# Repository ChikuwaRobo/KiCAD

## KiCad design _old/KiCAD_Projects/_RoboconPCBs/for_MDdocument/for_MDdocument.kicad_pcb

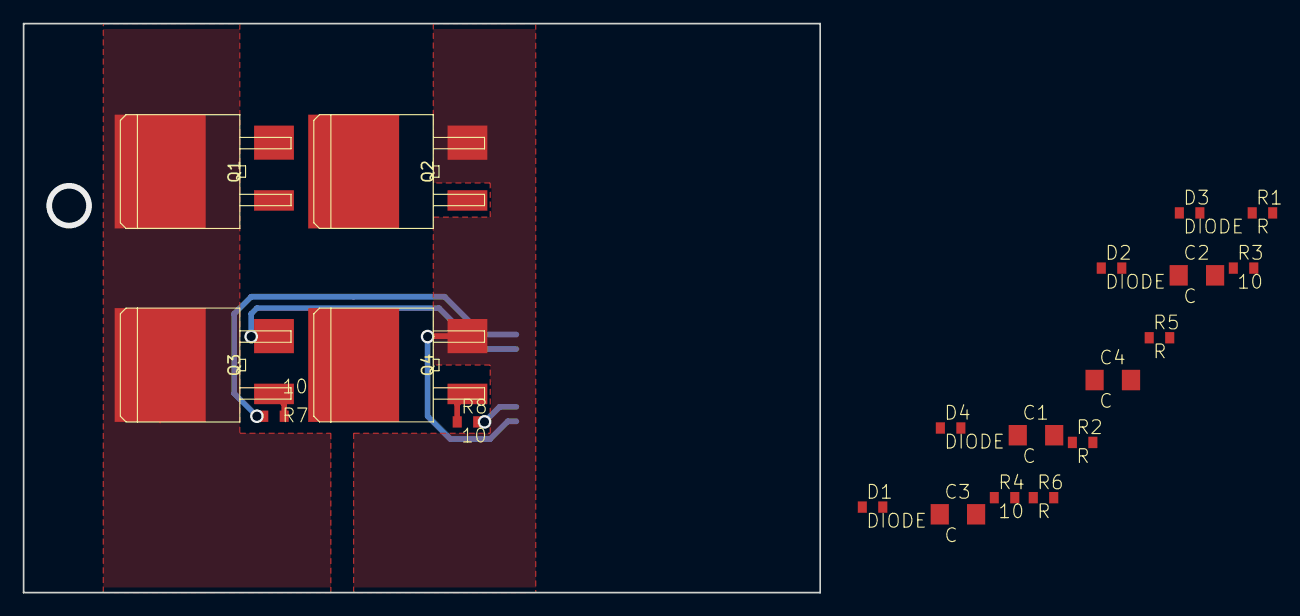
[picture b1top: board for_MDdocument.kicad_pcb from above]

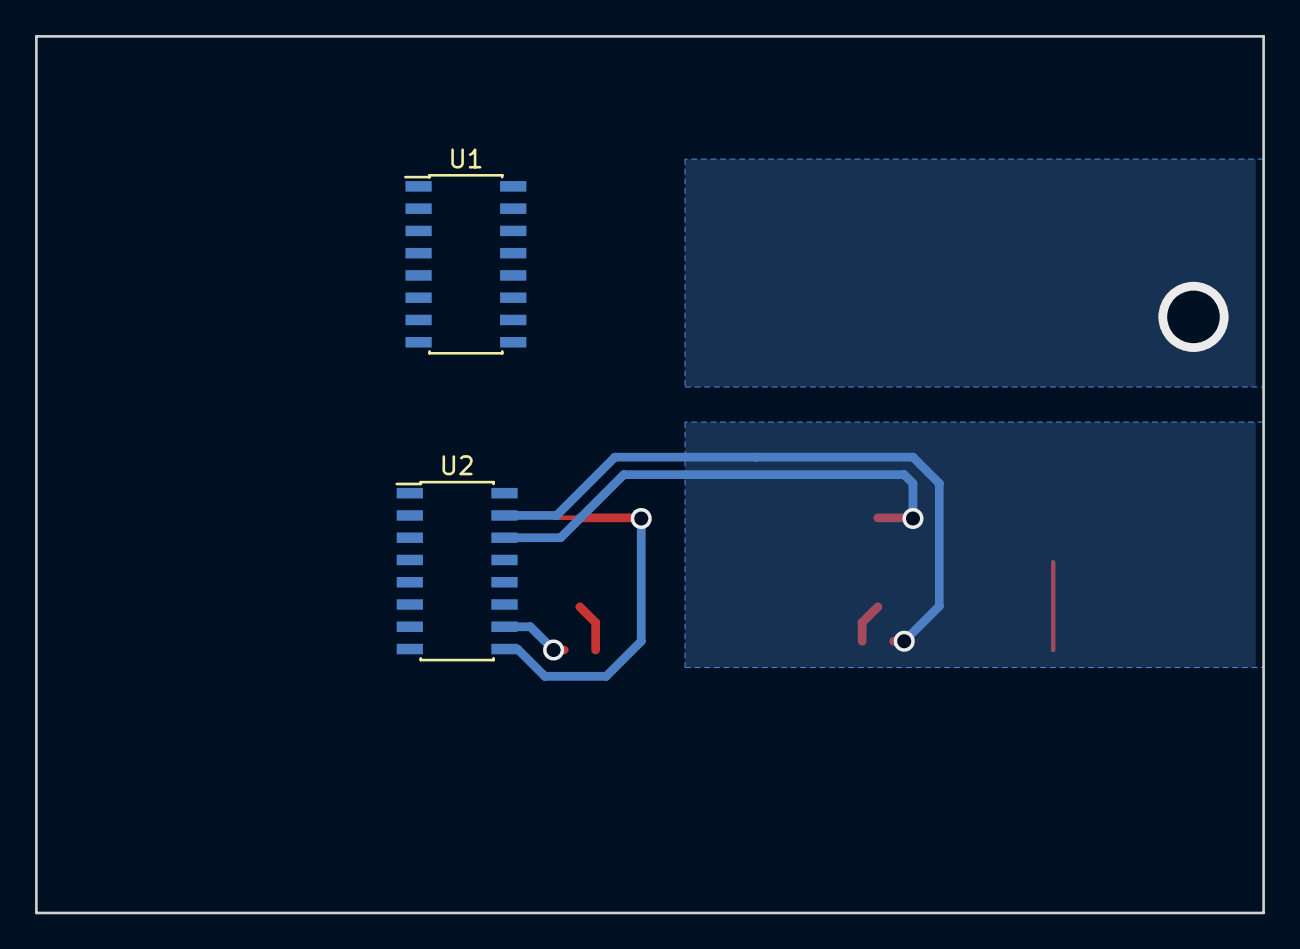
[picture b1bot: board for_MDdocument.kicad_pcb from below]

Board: 2 copper layers, 70.0 x 50.0 mm, 22 parts (2 on the bottom side), 21 nets.

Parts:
C1, C2, C3, C4: C; C3216
D1, D2, D3, D4: DIODE; C1608_WP
Q1, Q2, Q3, Q4: MOSFET_N; D2-PAK_compact
R1, R2, R5, R6: R; C1608_WP
R3, R4, R7, R8: 10; C1608_WP
U1, U2: SI8234; SOIC-16_3.9x9.9mm_Pitch1.27mm

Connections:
+BATT: Q1.D, Q3.D
/GD_12V: R1.1, R2.1, R5.1, R6.1
/OUT_A: C1.2, Q1.S, Q2.D, U1.14
/OUT_B: C3.2, Q3.S, Q4.D, U2.14
GNDPWR: C2.2, C4.2, Q2.S, Q4.S, U1.9, U2.9
unnamed: C1.1, D1.1, U1.16
unnamed: C2.1, D2.1, U1.11
unnamed: C3.1, D3.1, U2.16
unnamed: C4.1, D4.1, U2.11
unnamed: D1.2, R1.2
unnamed: D2.2, R2.2
unnamed: D3.2, R5.2
unnamed: D4.2, R6.2
unnamed: Q1.G, R3.1
unnamed: Q2.G, R4.1
unnamed: Q3.G, R7.1
unnamed: Q4.G, R8.1
unnamed: R3.2, U1.15
unnamed: R4.2, U1.10
unnamed: R7.2, U2.15
unnamed: R8.2, U2.10

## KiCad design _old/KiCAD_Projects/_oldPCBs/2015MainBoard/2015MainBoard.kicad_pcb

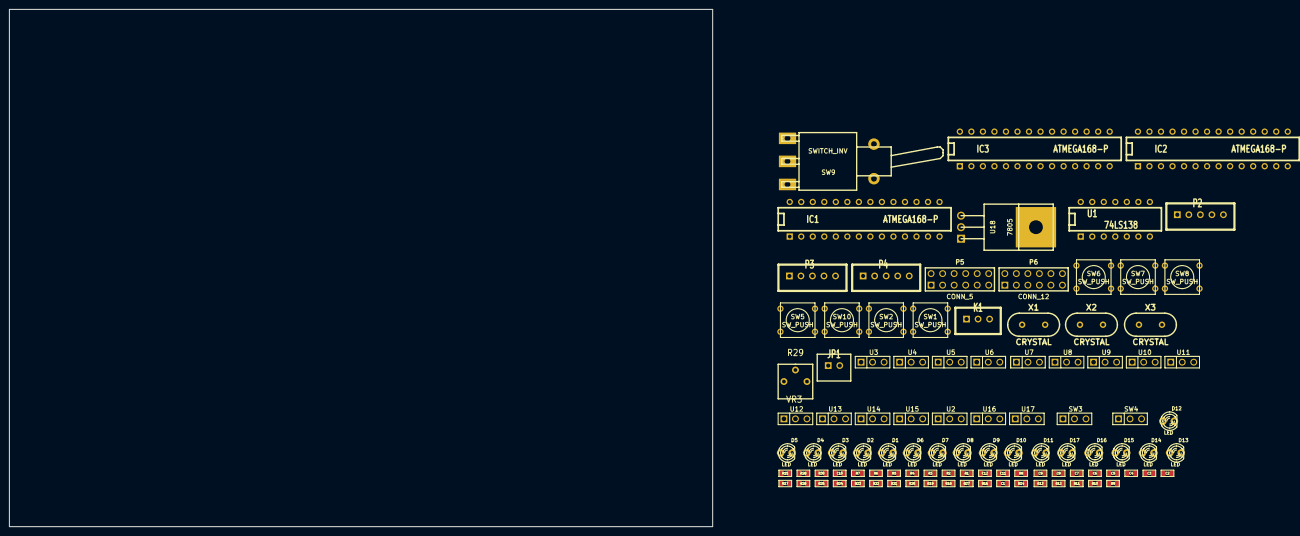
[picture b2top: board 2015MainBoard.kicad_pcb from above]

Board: 2 copper layers, 155.0 x 114.0 mm, 100 parts (0 on the bottom side), 73 nets, no tracks yet.

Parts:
C1, C2, C3, C4, C5, C6, C7, C8, C9, C10, C11, C12: C; SM0603
D1, D2, D3, D4, D5, D6, D7, D8, D9, D10, D11, D12, D13, D14, D15, D16, D17: LED; LED-3MM
IC1, IC2, IC3: ATMEGA168-P; DIP-28__300
JP1: JUMPER; XH2
K1: CONN_3; XH3
P2: DIL14; XH5
P3, P4: CONN_5; XH5
P5: CONN_5; pin_array_6x2
P6: CONN_12; pin_array_6x2
R1, R2, R3, R4, R5, R6, R7, R8, R9, R10, R11, R12, R13, R14, R15, R16, R17, R18, R19, R20, R21, R22, R23, R24, R25, R26, R27, R28, R30: R; SM0603
R29: VR3; RV2sq
SW1, SW2, SW5, SW6, SW7, SW8, SW10: SW_PUSH; SW_PUSH_SMALL
SW3, SW4: SWITCH_INV; PIN_ARRAY_3X1
SW9: SWITCH_INV; SW_SPDT
U1: 74LS138; DIP-14__300
U2, U3, U4, U5, U6, U7, U8, U9, U10, U11, U12, U13, U14, U15, U16, U17: IR; PIN_ARRAY_3X1
U18: 7805; TO220
X1, X2, X3: CRYSTAL; HC-49V

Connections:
+5V: C5.1, D2.1, D3.1, D4.1, D5.1, D6.1, D7.1, D8.1, D9.1, D10.1, D11.1, D12.1, D13.1, D14.1, D15.1, D16.1, D17.1, IC1.7, IC1.20, IC1.21, IC2.21, IC3.21, JP1.1, P3.1, P4.1, P5.1, P6.1, R2.1, R4.1, R15.1, R16.1, R17.2, R18.2, R28.1, R30.2, SW9.1, U2.3, U3.3, U4.3, U5.3, U6.3, U7.3, U8.3, U9.3, U10.3, U11.3, U12.3, U13.3, U14.3, U15.3, U16.3, U17.3
BallRST: IC2.1, P5.3, R1.2
BallRXD: IC2.2, P5.4, SW4.3
BallTXD: IC2.3, P5.5
DIS: D1.1, IC2.28
GND: C1.1, C2.1, C3.1, C4.1, C5.2, C6.2, C7.2, C8.1, C9.1, C10.2, C11.1, C12.1, IC1.8, IC1.22, IC2.22, IC3.22, K1.3, P3.2, P4.2, P5.2, P6.2, P6.5, P6.11, R5.2, R6.2, SW1.2, SW2.2, SW5.1, SW6.1, SW7.1, SW8.1, SW9.3, SW10.2, U1.8, U2.1, U3.1, U4.1, U5.1, U6.1, U7.1, U8.1, U9.1, U10.1, U11.1, U12.1, U13.1, U14.1, U15.1, U16.1, U17.1
IR0: IC2.14, R7.2, U2.2
IR1: IC2.15, R8.2, U3.2
IR2: IC2.16, R9.2, U4.2
IR3: IC2.17, R10.2, U5.2
IR4: IC2.18, R11.2, U6.2
IR5: IC2.19, R12.2, U7.2
IR6: IC2.23, R13.2, U8.2
IR7: IC2.24, R14.2, U9.2
IR8: IC2.25, R19.2, U10.2
IR9: IC2.26, R20.2, U11.2
IR10: IC2.4, R21.2, U12.2
IR11: IC2.5, R22.2, U13.2
IR12: IC2.6, R23.2, U14.2
IR13: IC2.11, R24.2, U15.2
IR14: IC2.12, R25.2, U16.2
IR15: IC2.13, R26.2, U17.2
MISO: IC1.18, IC3.18, P2.2
MODE: IC2.27, JP1.2, R6.1
MOSI: IC1.17, IC3.17, P2.1
MainRST: P3.3, R3.2
MainRXD_out: P3.4, SW3.1
MainTXD: IC1.3, SW4.2
MainTXD_out: P3.5, SW4.1
unnamed: C3.2, C4.2, IC2.10, X2.2
unnamed: IC3.4, P6.4
unnamed: IC3.5, P6.6
unnamed: IC3.11, P6.8
unnamed: IC3.13, P6.10
unnamed: P6.12, R30.1
unnamed: IC3.9, X3.1
unnamed: IC1.9, X1.1
unnamed: R1.1, R2.2, SW1.1
unnamed: R27.1, R28.2, SW10.1
unnamed: R3.1, R4.2, SW2.1
unnamed: IC3.12, P6.9
unnamed: IC3.6, P6.7
unnamed: U1.4, U1.5
unnamed: C1.2, C2.2, IC1.10, X1.2
unnamed: C11.2, C12.2, IC3.10, X3.2
unnamed: IC2.9, X2.1
unnamed: D2.2, R7.1
unnamed: D3.2, R8.1
unnamed: D4.2, R9.1
unnamed: D15.2, R24.1
unnamed: D16.2, R25.1
unnamed: D13.2, R22.1
unnamed: D14.2, R23.1
unnamed: D1.2, R5.1
unnamed: D17.2, R26.1
unnamed: D7.2, R12.1
unnamed: D6.2, R11.1
unnamed: D8.2, R13.1
unnamed: D5.2, R10.1
unnamed: D11.2, R20.1
unnamed: D12.2, R21.1
unnamed: D9.2, R14.1
unnamed: D10.2, R19.1
SCK: IC1.19, IC3.19, P2.3
SS1: P2.5, U1.14
SS3: IC3.16, U1.12
SW0: C6.1, IC1.4, R15.2, SW5.2
SW1: C7.1, IC1.6, R16.2, SW6.2
SW2: C8.2, IC1.25, R17.1, SW7.2
SW3: C9.2, IC1.26, R18.1, SW8.2
lcdRST: IC3.1, P4.3, R27.2
lcdRXD: IC3.2, P4.4
lcdTXD: IC3.3, P4.5

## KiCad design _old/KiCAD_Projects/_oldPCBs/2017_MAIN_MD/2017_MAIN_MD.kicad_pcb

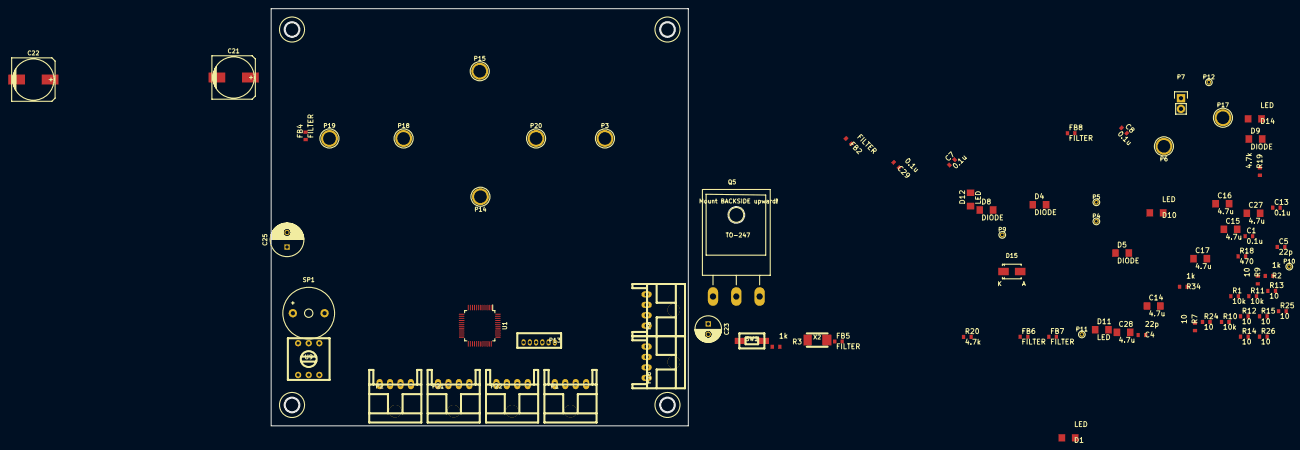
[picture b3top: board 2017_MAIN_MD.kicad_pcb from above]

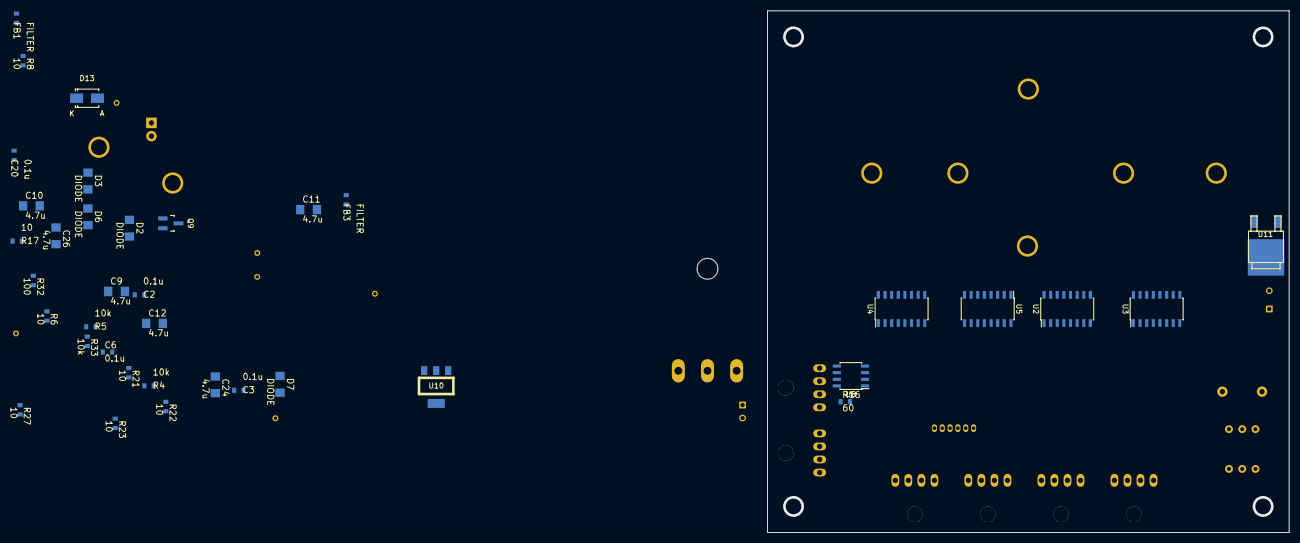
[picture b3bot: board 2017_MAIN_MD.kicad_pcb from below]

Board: 2 copper layers, 100.0 x 100.0 mm, 116 parts (37 on the bottom side), 87 nets, no tracks yet.

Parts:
C1, C2, C3, C6, C7, C8, C13, C20, C29: 0.1u; C1608_WP
C4, C5: 22p; C1608_WP
C9, C10, C11, C12, C14, C15, C16, C17, C24, C26, C27, C28: 4.7u; C3216
C21, C22: 470u; c_elec_10x10.5
C23: 100u; C_Radial_D6.3_L11.2_P2.5
C25: 100u; C_Radial_D8_L11.5_P3.5
D1, D10, D11, D12, D14: LED; C3216
D2, D3, D4, D5, D6, D7, D8, D9: DIODE; C3216
D13, D15: DIODE; SMA_Standard
FB1, FB2, FB3, FB4, FB5, FB6, FB7, FB8: FILTER; C1608_WP
P1, P2, P8, P16, P21, P22: CONN_01X04; XA_4LC
P3, P6, P14, P15, P17, P18, P19, P20: CONN_01X01; 1pin
P4, P5, P9, P10, P11, P12: TST; PINTST
P7: CONN_01X02; Pin_Header_Straight_1x02
P13: CONN_01X06; ZH_6T
Q5: MOSFET_N; TO-247_Horizontal_Neutral123_Reverse
Q9: MOSFET_N; SOT-23_Handsoldering
R1, R4, R5, R10, R11, R33: 10k; C1608_WP
R2, R3, R34: 1k; C1608_WP
R6, R7, R8, R9, R12, R13, R14, R15, R17, R21, R22, R23, R24, R25, R26, R27: 10; C1608_WP
R16: 60; C1608_WP
R18: 470; C1608_WP
R19, R20: 4.7k; C1608_WP
R32: 100; C1608_WP
SP1: SPEAKER; Buzzer_12x9.5RM7.6
SW1: SW_PUSH; RP_SMD_Button
U1: STM32F103_48; LQFP-48_7x7mm_Pitch0.5mm
U2, U3, U4, U5: SI8234; SOIC-16_3.9x9.9mm_Pitch1.27mm
U8: MAX3051; SOIC-8_3.9x4.9mm_Pitch1.27mm
U9: SW_ROTARY_16; rotary_0F
U10: NCP1117ST33T3G; TO-223
U11: NCP1117ST12T3G; SOT-428
X2: CRYSTAL; ABM3_2pads

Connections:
+3.3V: C2.2, C3.2, C6.2, C7.2, C8.2, C13.2, C20.2, C26.1, C29.2, D10.1, P1.2, P2.2, P5.1, P13.2, P21.2, P22.2, R1.1, U1.1, U1.9, U1.24, U1.36, U1.48, U2.3, U2.8, U3.3, U3.8, U4.3, U4.8, U5.3, U5.8, U8.3, U10.2
+12V: D11.1, D13.1, P8.2, P16.2, SP1.1
+BATT: C21.1, C22.1, D15.1, P14.1, P17.1, Q5.D
/BOOT0: R2.2, U1.44
/BUZZER: R32.2, U1.18
/CANH: P8.3, P16.3, R16.1, U8.7
/CANL: P7.1, P8.4, P16.4, U8.6
/CAN_RX: U1.32, U8.4
/CAN_TX: U1.33, U8.1
/ENC_Aa: P1.3, U1.10
/ENC_Ab: P1.4, U1.11
/ENC_Ba: P2.3, U1.16
/ENC_Bb: P2.4, U1.17
/GD_12V: C25.1, C28.1, D12.1, P12.1, R17.1, R21.1, R22.1, R23.1, R24.1, R25.1, R26.1, R27.1, U11.2
/LED_A: D14.1, U1.14
/LED_B: D1.1, U1.15
/LIMIT_A1: P21.3, U1.26
/LIMIT_A2: P21.4, U1.27
/LIMIT_B1: P22.3, U1.28
/LIMIT_B2: P22.4, U1.29
/MOTOR_EN: U1.25, U2.5, U3.5, U4.5, U5.5
/NRST: C1.2, R1.2, SW1.2, U1.7
/OSC_IN: C4.1, U1.5, X2.1
/OSC_OUT: C5.1, U1.6, X2.2
/OUT_A: C9.2, P18.1, U2.14
/OUT_AN: C11.2, P19.1, U3.14
/OUT_B: C14.2, P3.1, Q5.S, U4.14
/OUT_BN: C16.2, P20.1, U5.14
/PWM_A: U1.45, U2.1
/PWM_AN: U1.46, U3.1
/SEL_1: U1.19, U9.3
/SEL_2: U1.20, U9.1
/SEL_4: U1.21, U9.4
/SEL_8: U1.22, U9.6
/SWCLK: P13.3, U1.37
/SWDIO: P13.4, U1.34
/USART_RX: P13.6, U1.31
/USART_TX: P13.5, U1.30
GND: C1.1, C2.1, C3.1, C4.2, C5.2, C6.1, C7.1, C8.1, C13.1, C20.1, C23.2, C24.2, C26.2, C29.1, P1.1, P2.1, P8.1, P9.1, P13.1, P16.1, P21.1, P22.1, Q9.S, R2.1, R3.2, R4.2, R5.2, R10.2, R11.2, R18.2, R19.2, R33.2, R34.2, SW1.1, U1.8, U1.23, U1.35, U1.47, U2.4, U3.4, U4.4, U5.4, U8.2, U8.8, U9.2, U9.5, U10.1
GNDPWR: C10.2, C12.2, C15.2, C17.2, C21.2, C22.2, C25.2, C27.2, C28.2, P6.1, P11.1, P15.1, R20.2, U2.9, U3.9, U4.9, U5.9, U11.1
unnamed: C9.1, D2.2, U2.16
unnamed: C10.1, D6.2, U2.11
unnamed: C11.1, D3.2, U3.16
unnamed: C12.1, D7.2, U3.11
unnamed: C14.1, D4.2, U4.16
unnamed: C15.1, D8.2, U4.11
unnamed: C16.1, D5.2, U5.16
unnamed: C17.1, D9.2, U5.11
unnamed: C23.1, C24.1, D13.2, P4.1, U10.3
unnamed: C27.1, D15.2, P10.1, U11.3
unnamed: D1.2, R3.1
unnamed: D2.1, R21.2
unnamed: D3.1, R22.2
unnamed: D4.1, R17.2
unnamed: D5.1, R24.2
unnamed: D6.1, R23.2
unnamed: D7.1, R27.2
unnamed: D8.1, R25.2
unnamed: D9.1, R26.2
unnamed: D10.2, R18.1
unnamed: D11.2, R19.1
unnamed: D12.2, R20.1
unnamed: D14.2, R34.1
unnamed: FB1.1, R6.1
unnamed: FB2.1, R7.1
unnamed: FB3.1, R8.1
unnamed: FB4.1, R9.1
unnamed: FB5.1, R12.1
unnamed: FB5.2, Q5.G
unnamed: FB6.1, R13.1
unnamed: FB7.1, R14.1
unnamed: FB8.1, R15.1
unnamed: P7.2, R16.2
unnamed: Q9.D, SP1.2
unnamed: Q9.G, R32.1, R33.1
unnamed: R4.1, U2.6
unnamed: R5.1, U3.6
unnamed: R6.2, U2.15
unnamed: R7.2, U2.10
unnamed: R8.2, U3.15
unnamed: R9.2, U3.10
unnamed: R10.1, U4.6
unnamed: R11.1, U5.6
unnamed: R12.2, U4.15
unnamed: R13.2, U4.10
unnamed: R14.2, U5.15
unnamed: R15.2, U5.10

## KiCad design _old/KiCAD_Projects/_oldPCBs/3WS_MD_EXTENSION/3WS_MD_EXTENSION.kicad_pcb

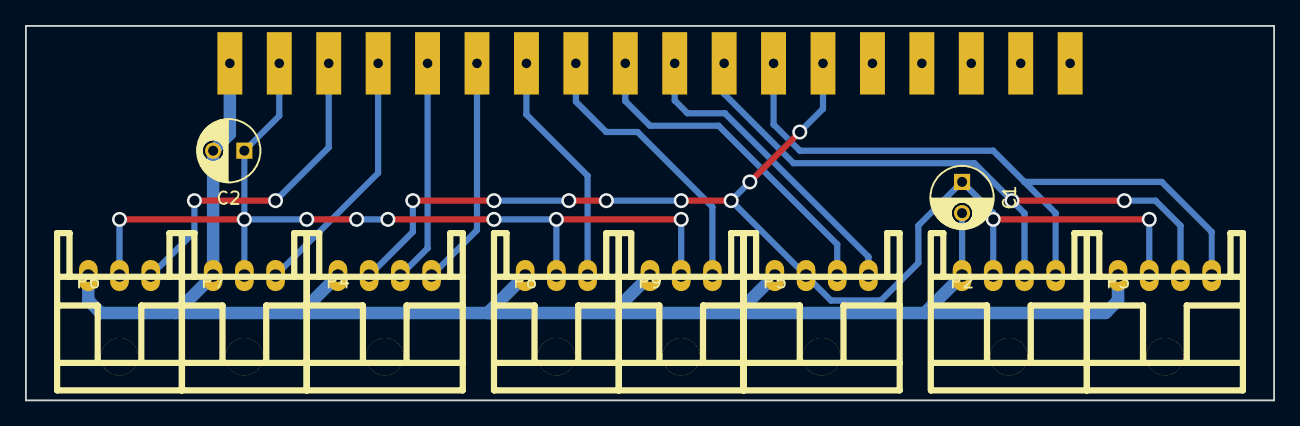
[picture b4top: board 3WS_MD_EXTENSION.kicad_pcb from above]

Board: 2 copper layers, 100.0 x 30.0 mm, 11 parts (1 on the bottom side), 13 nets.

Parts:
C1, C2: C; C_Radial_D5_L6_P2.5
P1: CONN_01X18; CardEdge_22(44type)_3.96mm_F
P2, P3, P4, P5: CONN_01X04; XA_4LC
P6, P7, P8, P9: CONN_01X03; XA_3LC

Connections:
+3.3V: C2.1, P1.2, P6.2, P7.2, P8.2, P9.2
+12V: C1.1, P1.13, P2.2, P3.2, P4.2, P5.2
/CAN_H: P1.11, P2.3, P3.3
/CAN_L: P1.12, P2.4, P3.4
/ENC_Aa: P1.5, P4.3
/ENC_Ab: P1.6, P4.4
/ENC_Ba: P1.9, P5.3
/ENC_Bb: P1.10, P5.4
/LIMIT_A1: P1.3, P6.3
/LIMIT_A2: P1.4, P7.3
/LIMIT_B1: P1.7, P8.3
/LIMIT_B2: P1.8, P9.3
GND: C1.2, C2.2, P1.1, P2.1, P3.1, P4.1, P5.1, P6.1, P7.1, P8.1, P9.1

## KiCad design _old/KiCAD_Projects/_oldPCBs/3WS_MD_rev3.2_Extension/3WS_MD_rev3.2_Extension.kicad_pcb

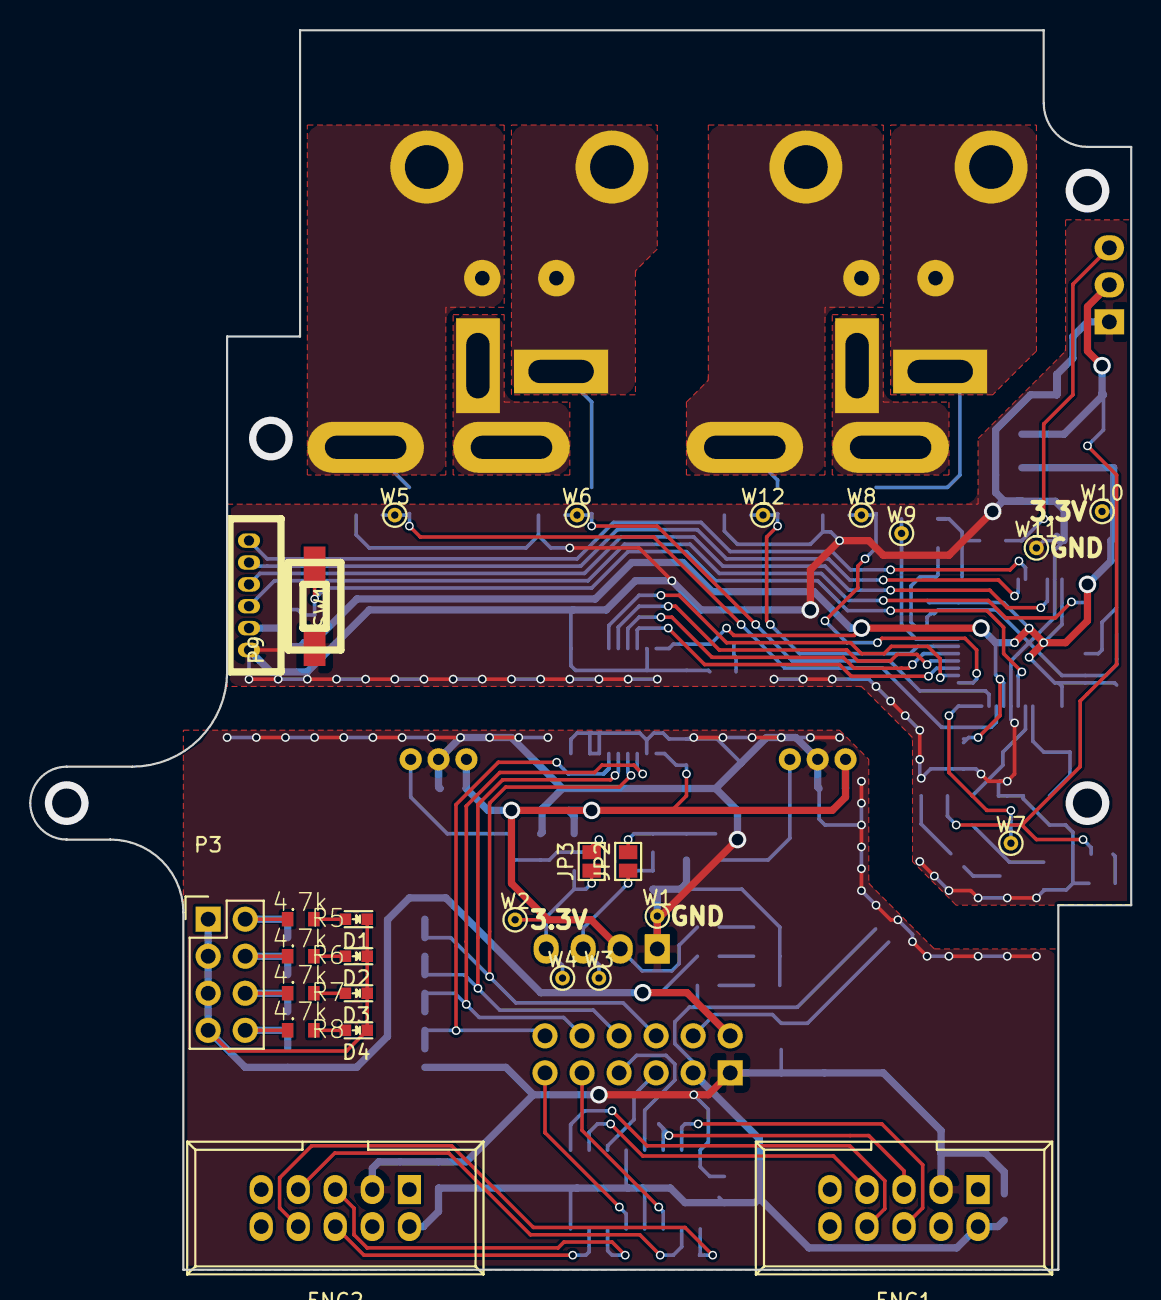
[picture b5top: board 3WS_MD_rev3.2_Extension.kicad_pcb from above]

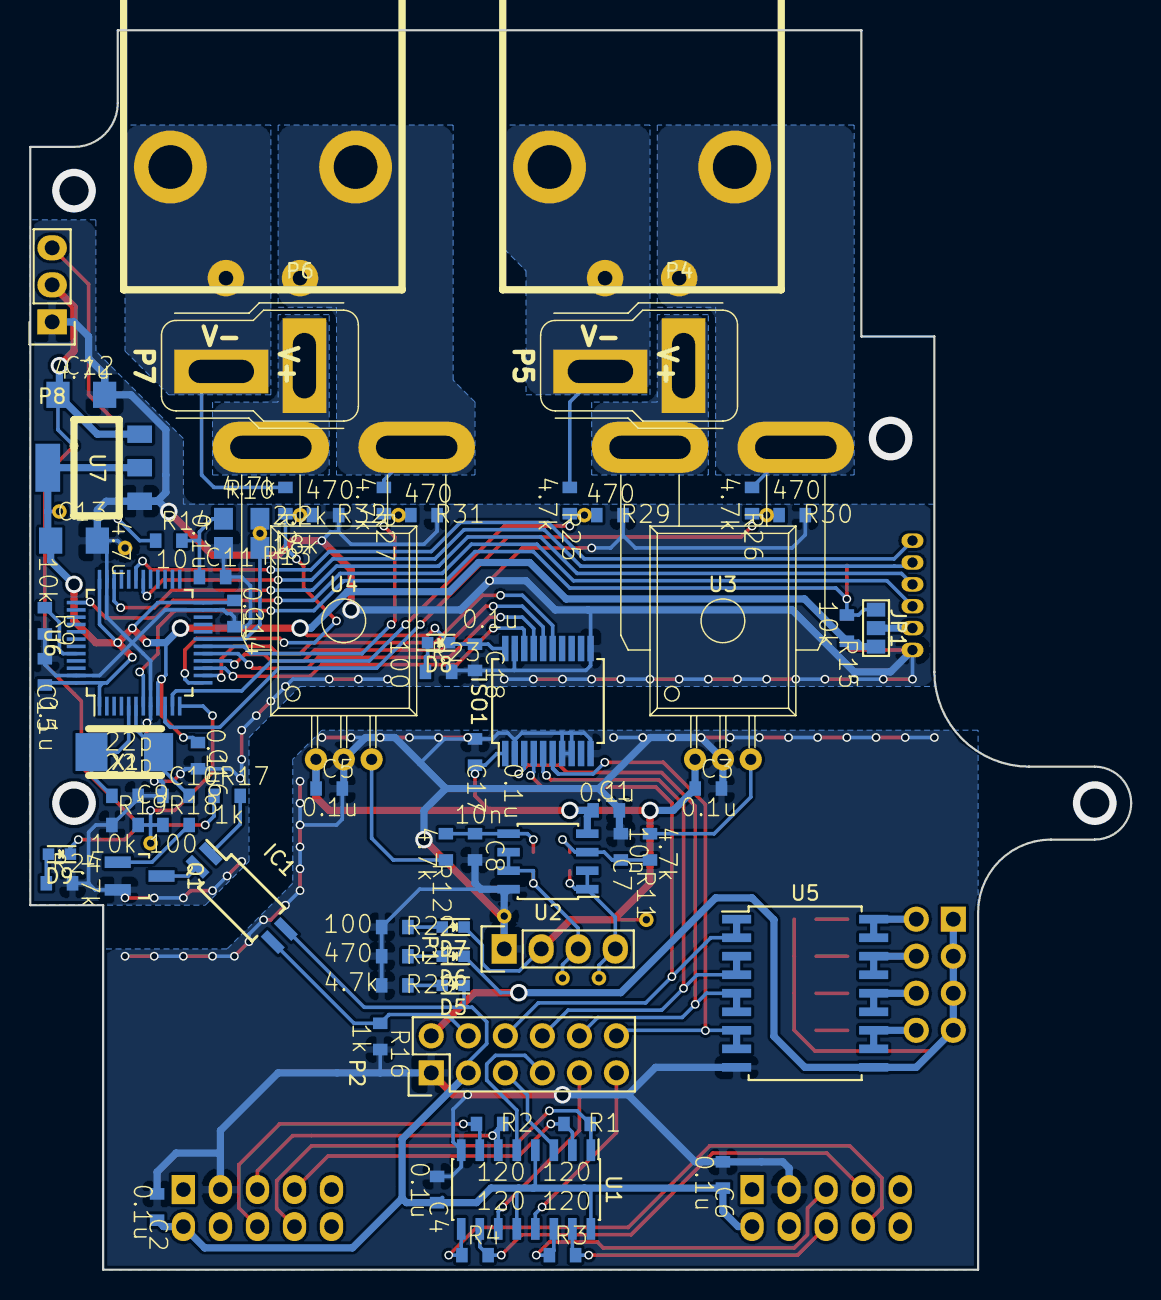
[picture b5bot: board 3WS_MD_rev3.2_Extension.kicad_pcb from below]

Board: 2 copper layers, 75.5 x 85.0 mm, 97 parts (70 on the bottom side), 73 nets.

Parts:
C1, C2, C3, C4, C5, C6, C11, C14, C15, C16, C17, C18: 0.1u; C1608_WP
C7, C8: 10n; C1608_WP
C9, C10: 22p; C1608_WP
C12, C13: 4.7u; C3216
D1, D2, D3, D4, D5, D6, D7, D8, D9: LED; LED_0603
ENC1, ENC2: RS422_ENCODER; DEF_ENCODER
IC1: TLP291; SOIJ-4_5.3x5.3mm_Pitch1.27mm
ISO1: ADuM3154; SSOP-20_5.3x7.2mm_Pitch0.65mm
JP1: JUMPER3; GS3
JP2, JP3: JUMPER; GS2
P1: CONN_01X04; Pin_Header_Straight_1x04
P2: CONN_02X06; Pin_Header_Straight_2x06
P3: CONN_02X04; Pin_Header_Straight_2x04
P4, P6: CONN_01X02; D-3200S_2L_PW
P5, P7: CONN_01X02; DEANS_T_M
P8: CONN_01X03; Pin_Header_Straight_1x03
P9: CONN_01X06; ZH_6T
Q1: MOSFET_N; SOT-23_Handsoldering
R1, R2, R3, R4: 120; C1608_WP
R5, R6, R7, R8, R11, R12, R20, R24, R25, R26, R27, R28: 4.7k; C1608_WP
R9, R15, R19: 10k; C1608_WP
R10: 18k; C2012
R13: 2.2k; C2012
R14: 10; C1608_WP
R16, R17: 1k; C1608_WP
R18, R22, R23: 100; C1608_WP
R21, R29, R30, R31, R32: 470; C1608_WP
SW1: SW_PUSH; RP_SMD_Button
U1: SN75175; SOIC-16_3.9x9.9mm_Pitch1.27mm
U2: LM358; SOIC-8_3.9x4.9mm_Pitch1.27mm
U3, U4: ACS758; ACS785xCB
U5: TBD62083A; SOIC-18_7.5x11.6mm_Pitch1.27mm
U6: STM32F103_48; LQFP-48_7x7mm_Pitch0.5mm
U7: NCP1117ST33T3G; SOT-223_reg
W1, W2, W3, W4, W5, W6, W7, W8, W9, W10, W11, W12: TEST_1P; PINTST
X1: CRYSTAL; ABM3_2pads

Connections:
+3.3V: C1.1, C3.1, C5.1, C17.1, D7.1, ISO1.1, P1.2, U2.4, U3.1, U4.1, W2.1
+5V: C2.1, C4.1, C6.1, D5.1, ENC1.2, ENC2.2, IC1.4, P2.3, U1.4, U1.12, U1.16
+12V: D1.1, D2.1, D3.1, D4.1, D6.1, P2.2, P3.1, P3.3, P3.5, P3.7, U5.10
+BATT: P8.3, R14.1
/BATT_IN: R10.2, R13.1, U6.19, W9.1
/ENC_Aa: P2.5, U1.3
/ENC_Aaa: ENC1.7, R1.2, U1.2
/ENC_Aab: ENC1.8, R1.1, U1.1
/ENC_Ab: P2.7, U1.5
/ENC_Aba: ENC1.5, R2.1, U1.6
/ENC_Abb: ENC1.6, R2.2, U1.7
/ENC_Ba: P2.9, U1.11
/ENC_Baa: ENC2.7, R4.2, U1.10
/ENC_Bab: ENC2.8, R4.1, U1.9
/ENC_Bb: P2.11, U1.13
/ENC_Bba: ENC2.5, R3.1, U1.14
/ENC_Bbb: ENC2.6, R3.2, U1.15
/EXIO_0: JP2.1, P1.3, U2.6, U2.7, W3.1
/EXIO_1: JP3.1, P1.4, U2.1, U2.2, W4.1
/GD_12V: C12.1, D9.1, P8.2, R17.1, U7.3
/NRST: JP1.1, R15.2, SW1.1, U6.7
/OUT_0: P3.2, R5.2, U5.17, U5.18
/OUT_1: P3.4, R6.2, U5.15, U5.16
/OUT_2: P3.6, R7.2, U5.13, U5.14
/OUT_3: P3.8, R8.2, U5.11, U5.12
/PW_3.3V: C13.1, C14.1, C15.1, C16.1, C18.1, D8.1, ISO1.20, JP1.3, R15.1, U6.1, U6.9, U6.24, U6.36, U6.48, U7.2, W10.1
/SPI_MISO: ISO1.16, U6.16
/SPI_MOSI: ISO1.17, U6.17
/SPI_NSS: ISO1.15, U6.14
/SPI_SCK: ISO1.18, U6.15
/SWDCK: P9.3, U6.37
/SWDIO: P9.4, U6.34
/USART_RX: P9.6, U6.31
/USART_TX: P9.5, U6.30
/V0A_IN: R27.1, R31.2, W12.1
/V0B_IN: R28.1, R32.2, U6.13, W8.1
/V1A_IN: R26.1, R30.2, U6.10, W5.1
/V1B_IN: R25.1, R29.2, U6.11, W6.1
/VALVE_0: ISO1.6, P2.12, U5.7, U5.8
/VALVE_1: ISO1.3, P2.10, U5.5, U5.6
/VALVE_2: ISO1.5, P2.8, U5.3, U5.4
/VALVE_3: ISO1.4, P2.6, U5.1, U5.2
/V_0A: P6.1, R27.2, U4.4
/V_0B: P6.2, P7.2, R28.2
/V_1A: P4.1, R26.2, U3.4
/V_1B: P4.2, P5.2, R25.2
/V_RX: IC1.3, P2.4, R16.1
/V_TX: R18.1, R19.2, U6.12, W7.1
GND: C1.2, C2.2, C3.2, C4.2, C5.2, C6.2, C7.2, C8.2, C17.2, ENC1.3, ENC2.3, ISO1.2, ISO1.7, ISO1.8, ISO1.10, P1.1, P2.1, R16.2, R20.2, R21.2, R22.2, U1.8, U2.8, U3.2, U4.2, U5.9, W1.1
GNDPWR: C9.1, C10.1, C11.2, C12.2, C13.2, C14.2, C15.2, C16.2, C18.2, ISO1.11, ISO1.19, P8.1, P9.1, Q1.S, R9.2, R13.2, R19.1, R23.2, R24.2, R29.1, R30.1, R31.1, R32.1, SW1.2, U6.8, U6.23, U6.35, U6.47, U7.1, W11.1
unnamed: C7.1, JP3.2, R11.2, U2.3
unnamed: C8.1, JP2.2, R12.2, U2.5
unnamed: C9.2, U6.5, X1.1
unnamed: C10.2, U6.6, X1.2
unnamed: C11.1, R10.1, R14.2
unnamed: D1.2, R5.1
unnamed: D2.2, R6.1
unnamed: D3.2, R7.1
unnamed: D4.2, R8.1
unnamed: D5.2, R20.1
unnamed: D6.2, R21.1
unnamed: D7.2, R22.1
unnamed: D8.2, R23.1
unnamed: D9.2, R24.1
unnamed: IC1.1, R17.2
unnamed: IC1.2, Q1.D
unnamed: JP1.2, P9.2
unnamed: P5.1, U3.5
unnamed: P7.1, U4.5
unnamed: Q1.G, R18.2
unnamed: R9.1, U6.44
unnamed: R11.1, U3.3
unnamed: R12.1, U4.3

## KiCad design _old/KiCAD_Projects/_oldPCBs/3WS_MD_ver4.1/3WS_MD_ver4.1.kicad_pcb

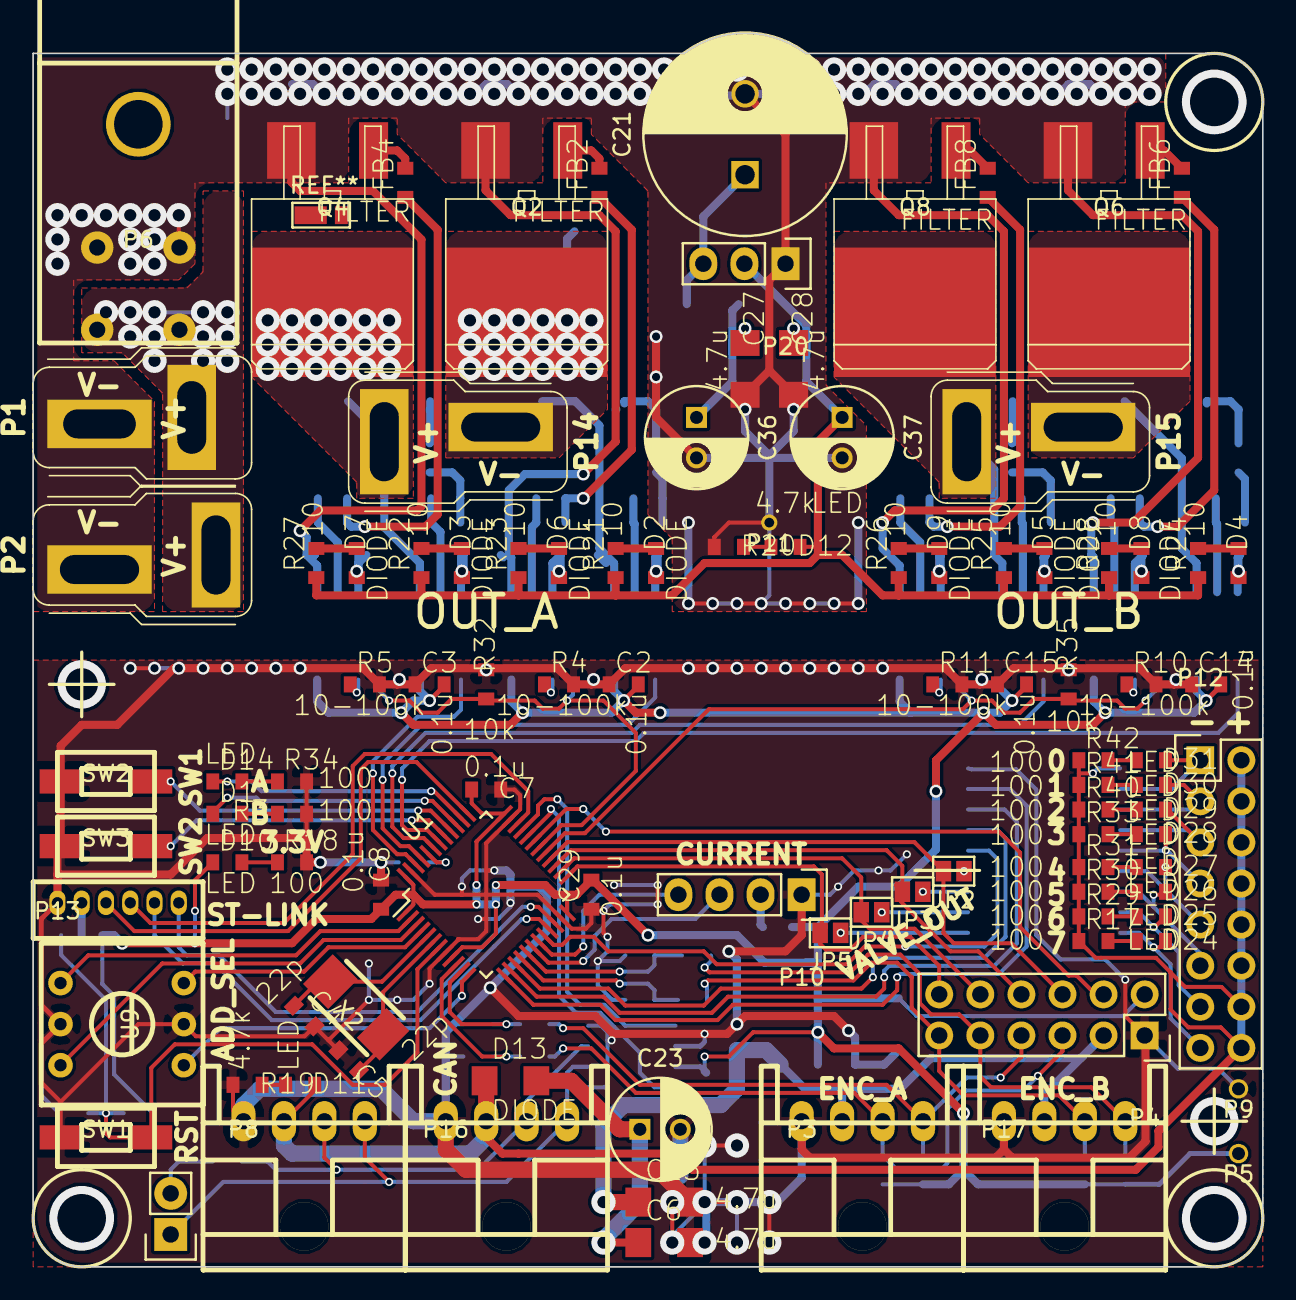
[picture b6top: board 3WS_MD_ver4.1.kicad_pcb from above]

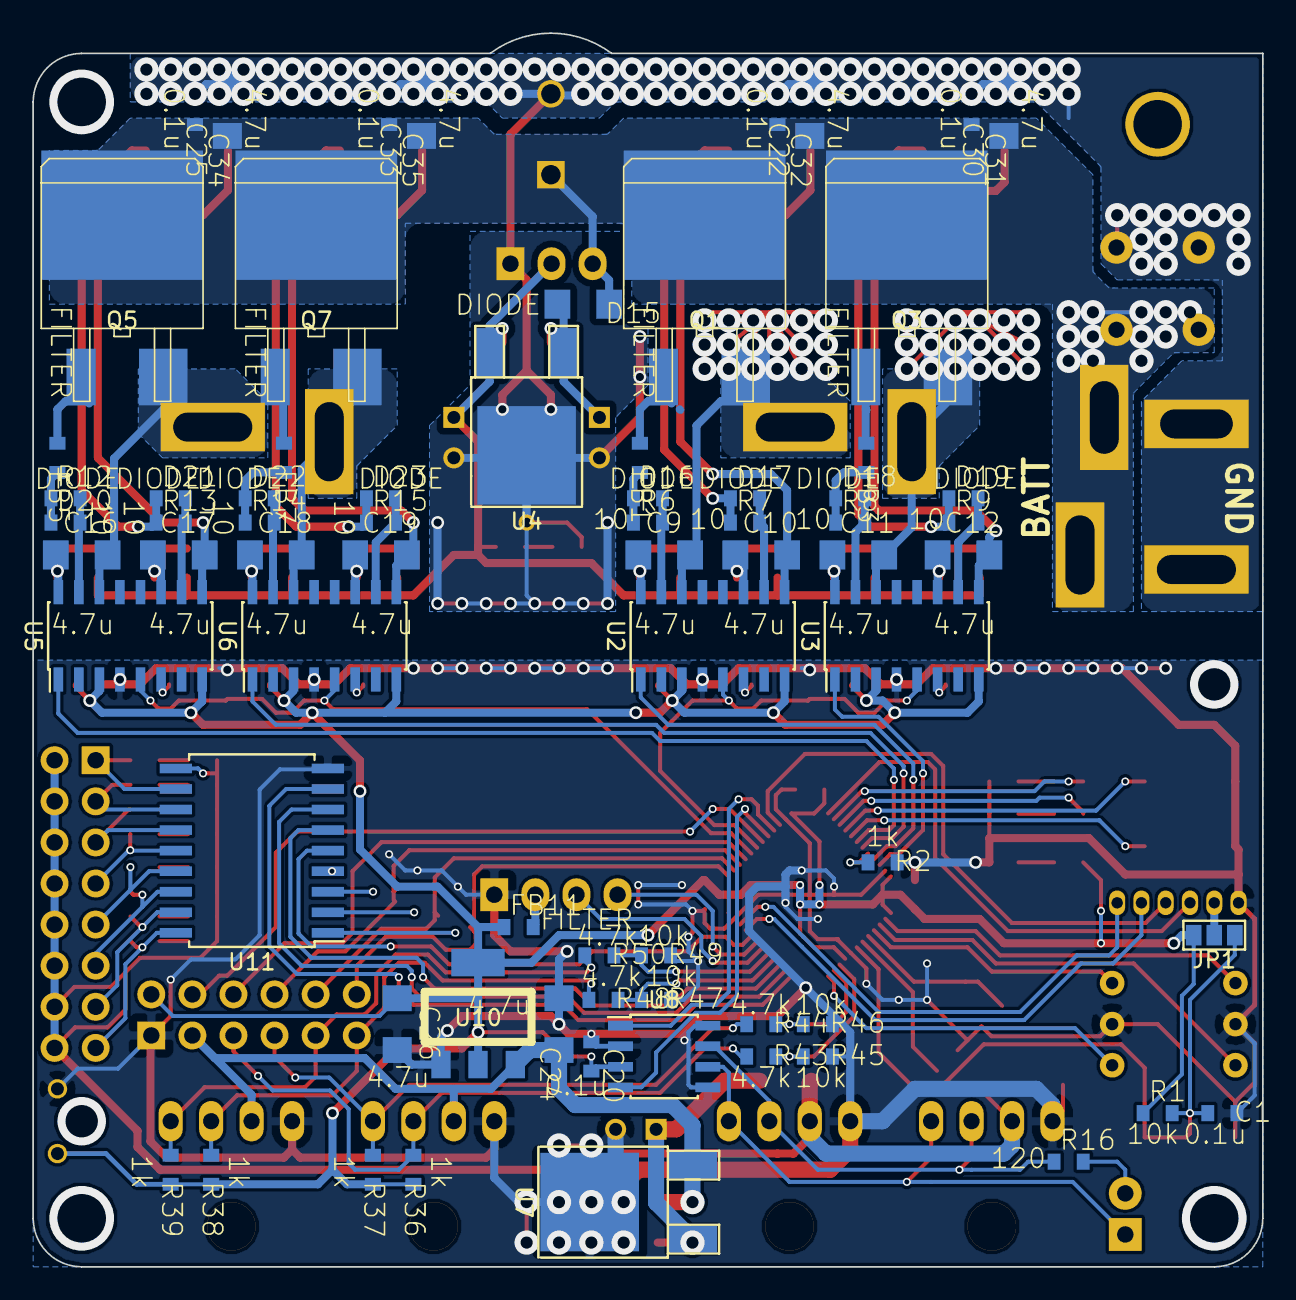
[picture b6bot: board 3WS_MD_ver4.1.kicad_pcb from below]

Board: 2 copper layers, 76.0 x 76.2 mm, 173 parts (71 on the bottom side), 130 nets.

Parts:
C1, C2, C3, C7, C8, C14, C15, C20, C22, C25, C29, C30, C33: 0.1u; C1608_WP
C4, C5: 22p; C1608_WP
C6, C9, C10, C11, C12, C13, C16, C17, C18, C19, C24, C26, C27, C28, C31, C32, C34, C35: 4.7u; C3216
C21: 470u; C_Radial_D12.5_L25_P5
C23, C36, C37: 100u; C_Radial_D6.3_L11.2_P2.5
D1, D10, D11, D12, D14, D24, D25, D26, D27, D28, D29, D30, D31: LED; C1608_WP
D2, D3, D4, D5, D6, D7, D8, D9, D16, D17, D18, D19, D20, D21, D22, D23: DIODE; C1608_WP
D13, D15: DIODE; C3216
FB1, FB2, FB3, FB4, FB5, FB6, FB7, FB8, FB11: FILTER; C1608_WP
JP1: JUMPER3; GS3
JP2, JP3, JP4, JP5: JUMPER; GS2
P1: CONN_01X02; DEANS_T_M
P2, P14, P15: CONN_01X02; DEANS_T_F
P3, P8, P16, P17: CONN_01X04; XA_4LC
P4: CONN_02X06; Socket_Strip_Straight_2x06
P5, P9, P11: TST; testPin
P6: CONN_01X04; D-3500D_4S
P7: CONN_01X02; Pin_Header_Straight_1x02
P10: CONN_01X04; Socket_Strip_Straight_1x04
P12: CONN_02X08; Pin_Header_Straight_2x08
P13: CONN_01X06; ZH_6T
P20: CONN_01X03; Socket_Strip_Straight_1x03
Q1, Q2, Q3, Q4, Q5, Q6, Q7, Q8: MOSFET_N; D2-PAK_compact
R1, R32, R35, R45, R46, R47, R49: 10k; C1608_WP
R2, R36, R37, R38, R39: 1k; C1608_WP
R3, R17, R18, R29, R30, R31, R33, R34, R40, R41, R42: 100; C1608_WP
R4, R5, R10, R11: 10-100k; C1608_WP
R6, R7, R8, R9, R12, R13, R14, R15, R21, R22, R23, R24, R25, R26, R27, R28: 10; C1608_WP
R16: 120; C1608_WP
R19, R20, R43, R44, R48, R50: 4.7k; C1608_WP
SW1, SW2, SW3: SW_PUSH; RP_SMD_Button
U1: STM32F103_48; LQFP-48_7x7mm_Pitch0.5mm
U2, U3, U5, U6: SI8234; SOIC-16_3.9x9.9mm_Pitch1.27mm
U4: LM7812; TO-252-2Lead_regu
U7: 7805; TO-252-2Lead_regu
U8: MAX3051; SOIC-8_3.9x4.9mm_Pitch1.27mm
U9: SW_ROTARY_16; rotary_0F
U10: NCP1117ST33T3G; SOT-223_reg
U11: TBD62083A; SOIC-18_7.5x11.6mm_Pitch1.27mm
X2: CRYSTAL; ABM3_2pads

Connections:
+3.3V: C2.2, C3.2, C7.2, C8.2, C14.2, C15.2, C20.2, C26.1, C29.2, D10.1, FB11.1, JP1.3, P4.2, P5.1, R1.1, R36.1, R37.1, R38.1, R39.1, U1.1, U1.9, U1.24, U1.36, U1.48, U2.3, U2.8, U3.3, U3.8, U5.3, U5.8, U6.3, U6.8, U8.3, U10.2
+5V: C13.1, C24.1, P3.2, P4.3, P17.2, U7.VO, U10.3
+12V: D11.1, D13.1, P8.2, P12.2, P12.4, P12.6, P12.8, P12.10, P12.12, P12.14, P12.16, P16.2, R17.1, R29.1, R30.1, R31.1, R33.1, R40.1, R41.1, R42.1, U11.10
+BATT: C21.1, C22.1, C25.1, C30.1, C31.1, C32.1, C33.1, C34.1, C35.1, D15.1, P1.1, P2.1, P6.2, P6.4, P20.3, Q1.D, Q3.D, Q5.D, Q7.D
/BOOT0: R2.2, U1.44
/CANH: P8.3, P16.3, R16.1, U8.7
/CANL: P7.1, P8.4, P16.4, U8.6
/CAN_RX: U1.32, U8.4
/CAN_TX: U1.33, U8.1
/ENC_Aa: P3.3, P4.5, R36.2, R43.2
/ENC_Ab: P3.4, P4.7, R37.2, R44.2
/ENC_Ba: P4.11, P17.3, R38.2, R48.2
/ENC_Bb: P4.9, P17.4, R39.2, R50.2
/EXIO_0: P10.3, U1.18
/EXIO_1: P10.4, U1.19
/GD_12V: C28.1, C37.1, D12.1, P20.2, R21.1, R22.1, R23.1, R24.1, R25.1, R26.1, R27.1, R28.1, U4.VO
/LED_A: D14.1, U1.38
/LED_B: D1.1, U1.39
/MOTORA_EN: R32.2, U1.30, U2.5, U3.5
/MOTORB_EN: R35.2, U1.29, U5.5, U6.5
/NRST: C1.2, JP1.1, R1.2, SW1.2, U1.7
/OSC_IN: C4.1, U1.5, X2.1
/OSC_OUT: C5.1, U1.6, X2.2
/OUT_0: D31.1, P12.1, U11.11
/OUT_1: D30.1, P12.3, U11.12
/OUT_2: D29.1, P12.5, U11.13
/OUT_3: D28.1, P12.7, U11.14
/OUT_4: D27.1, P12.9, U11.15
/OUT_5: D26.1, P12.11, U11.16
/OUT_6: D25.1, P12.13, U11.17
/OUT_7: D24.1, P12.15, U11.18
/OUT_A: C9.2, P14.2, Q1.S, Q2.D, U2.14
/OUT_AN: C11.2, P14.1, Q3.S, Q4.D, U3.14
/OUT_B: C16.2, P15.2, Q5.S, Q6.D, U5.14
/OUT_BN: C18.2, P15.1, Q7.S, Q8.D, U6.14
/PWM_A: U1.45, U2.1
/PWM_AN: U1.46, U3.1
/PWM_B: U1.42, U5.1
/PWM_BN: U1.43, U6.1
/SEL_1: U1.4, U9.3
/SEL_2: U1.12, U9.1
/SEL_4: U1.2, U9.4
/SEL_8: U1.3, U9.6
/SPI_MISO: JP3.2, P4.8, U1.27
/SPI_MOSI: JP2.2, P4.6, U1.28
/SPI_NSS: JP5.2, P4.12, U1.25
/SPI_SCK: JP4.2, P4.10, U1.26
/SW1: SW2.2, U1.40
/SW2: SW3.2, U1.41
/SWCLK: P13.3, U1.37
/SWDIO: P13.4, U1.34
/USART_RX: P13.6, U1.22
/USART_TX: P13.5, U1.21
/VALVE_0: U1.13, U11.8
/VALVE_1: U1.14, U11.7
/VALVE_2: U1.15, U11.6
/VALVE_3: U1.20, U11.5
/VALVE_4: JP2.1, U11.4
/VALVE_5: JP3.1, U11.3
/VALVE_6: JP4.1, U11.2
/VALVE_7: JP5.1, U11.1
/V_RX: P4.4, U1.31
GND: C1.1, C2.1, C3.1, C4.2, C5.2, C6.2, C7.1, C8.1, C13.2, C14.1, C15.1, C20.1, C23.2, C24.2, C26.2, C29.1, P3.1, P4.1, P8.1, P9.1, P10.1, P13.1, P16.1, P17.1, R2.1, R3.2, R4.2, R5.2, R10.2, R11.2, R18.2, R19.2, R32.1, R34.2, R35.1, R45.1, R46.1, R47.1, R49.1, SW1.1, SW2.1, SW3.1, U1.8, U1.23, U1.35, U1.47, U2.4, U3.4, U5.4, U6.4, U7.GND, U8.2, U8.5, U8.8, U9.2, U9.5, U10.1, U11.9
GNDPWR: C10.2, C12.2, C17.2, C19.2, C21.2, C22.2, C25.2, C27.2, C28.2, C30.2, C31.2, C32.2, C33.2, C34.2, C35.2, C36.2, C37.2, P1.2, P2.2, P6.1, P6.3, P11.1, P20.1, Q2.S, Q4.S, Q6.S, Q8.S, R20.2, U2.9, U3.9, U4.GND, U5.9, U6.9
unnamed: C9.1, D2.2, U2.16
unnamed: C10.1, D6.2, U2.11
unnamed: C11.1, D3.2, U3.16
unnamed: C12.1, D7.2, U3.11
unnamed: C16.1, D4.2, U5.16
unnamed: C17.1, D8.2, U5.11
unnamed: C18.1, D5.2, U6.16
unnamed: C19.1, D9.2, U6.11
unnamed: C6.1, C23.1, D13.2, U7.VI
unnamed: C27.1, C36.1, D15.2, U4.VI
unnamed: D1.2, R3.1
unnamed: D2.1, R21.2
unnamed: D3.1, R22.2
unnamed: D4.1, R24.2
unnamed: D5.1, R25.2
unnamed: D6.1, R23.2
unnamed: D7.1, R27.2
unnamed: D8.1, R28.2
unnamed: D9.1, R26.2
unnamed: D10.2, R18.1
unnamed: D11.2, R19.1
unnamed: D12.2, R20.1
unnamed: D14.2, R34.1
unnamed: D16.1, FB1.1, R6.1
unnamed: D16.2, R6.2, U2.15
unnamed: D17.1, FB2.1, R7.1
unnamed: D17.2, R7.2, U2.10
unnamed: D18.1, FB3.1, R8.1
unnamed: D18.2, R8.2, U3.15
unnamed: D19.1, FB4.1, R9.1
unnamed: D19.2, R9.2, U3.10
unnamed: D20.1, FB5.1, R12.1
unnamed: D20.2, R12.2, U5.15
unnamed: D21.1, FB6.1, R13.1
unnamed: D21.2, R13.2, U5.10
unnamed: D22.1, FB7.1, R14.1
unnamed: D22.2, R14.2, U6.15
unnamed: D23.1, FB8.1, R15.1
unnamed: D23.2, R15.2, U6.10
unnamed: D24.2, R17.2
unnamed: D25.2, R29.2
unnamed: D26.2, R30.2
unnamed: D27.2, R31.2
unnamed: D28.2, R33.2
unnamed: D29.2, R40.2
unnamed: D30.2, R41.2
unnamed: D31.2, R42.2
unnamed: FB1.2, Q1.G
unnamed: FB2.2, Q2.G
unnamed: FB3.2, Q3.G
unnamed: FB4.2, Q4.G
unnamed: FB5.2, Q5.G
unnamed: FB6.2, Q6.G
unnamed: FB7.2, Q7.G
unnamed: FB8.2, Q8.G
unnamed: FB11.2, P10.2
unnamed: JP1.2, P13.2
unnamed: P7.2, R16.2
unnamed: R4.1, U2.6
unnamed: R5.1, U3.6
unnamed: R10.1, U5.6
unnamed: R11.1, U6.6
unnamed: R43.1, R45.2, U1.10
unnamed: R44.1, R46.2, U1.11
unnamed: R47.2, R48.1, U1.16
unnamed: R49.2, R50.1, U1.17
